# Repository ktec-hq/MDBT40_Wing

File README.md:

# MDBT40 BT4.0 Module Wing
This repo is published under CC-BY-SA 4.0 License

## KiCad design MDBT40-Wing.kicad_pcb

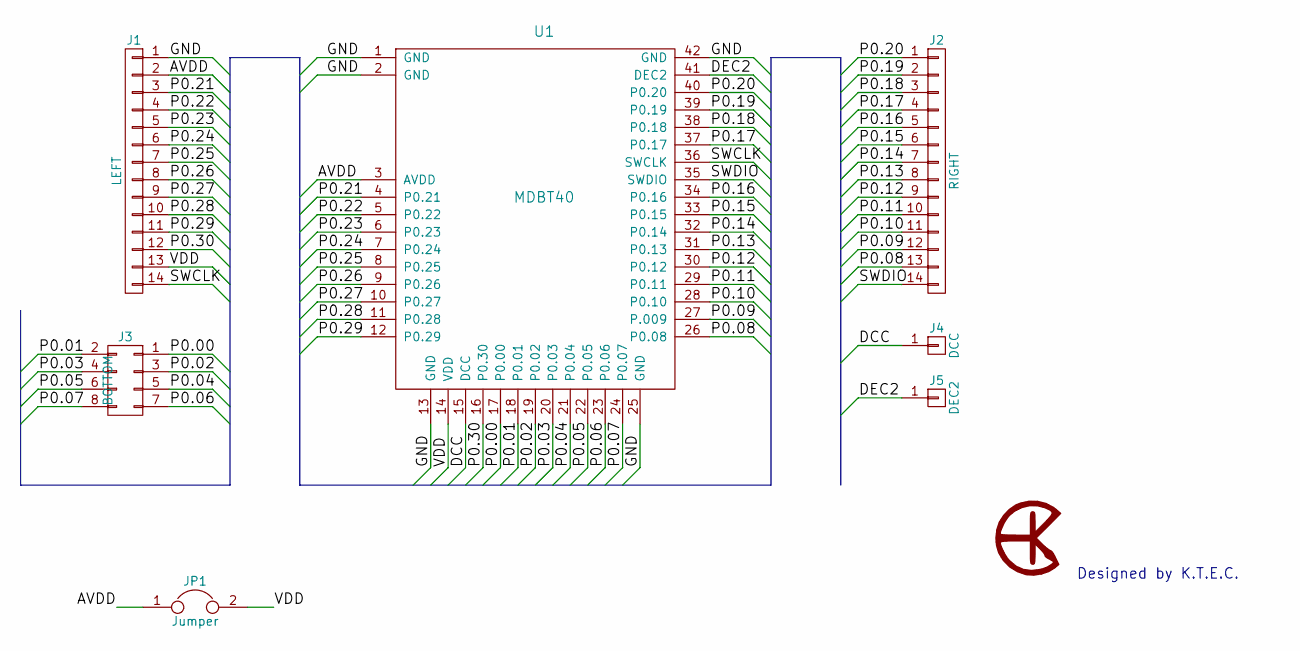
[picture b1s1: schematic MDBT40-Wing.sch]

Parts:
J1: LEFT; Pin_Header_Straight_1x14_Pitch2.54mm
J2: RIGHT; Pin_Header_Straight_1x14_Pitch2.54mm
J3: BOTTOM; Pin_Header_Straight_1x08_Pitch2.54mm
J4: DCC; 1Pin
J5: DEC2; 1Pin
JP1: Jumper; GS2
U1: MDBT40; MDBT40-Carrier

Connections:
/AVDD: J1.2, JP1.1, U1.3 (AVDD)
/DCC: J4.1, U1.15 (DCC)
/DEC2: J5.1, U1.41 (DEC2)
/GND: J1.1, U1.1 (GND), U1.2 (GND), U1.13 (GND), U1.25 (GND), U1.42 (GND)
/P0.00: J3.1, U1.17 (P0.00)
/P0.01: J3.2, U1.18 (P0.01)
/P0.02: J3.3, U1.19 (P0.02)
/P0.03: J3.4, U1.20 (P0.03)
/P0.04: J3.5, U1.21 (P0.04)
/P0.05: J3.6, U1.22 (P0.05)
/P0.06: J3.7, U1.23 (P0.06)
/P0.07: J3.8, U1.24 (P0.07)
/P0.08: J2.13, U1.26 (P0.08)
/P0.09: J2.12, U1.27 (P.009)
/P0.10: J2.11, U1.28 (P0.10)
/P0.11: J2.10, U1.29 (P0.11)
/P0.12: J2.9, U1.30 (P0.12)
/P0.13: J2.8, U1.31 (P0.13)
/P0.14: J2.7, U1.32 (P0.14)
/P0.15: J2.6, U1.33 (P0.15)
/P0.16: J2.5, U1.34 (P0.16)
/P0.17: J2.4, U1.37 (P0.17)
/P0.18: J2.3, U1.38 (P0.18)
/P0.19: J2.2, U1.39 (P0.19)
/P0.20: J2.1, U1.40 (P0.20)
/P0.21: J1.3, U1.4 (P0.21)
/P0.22: J1.4, U1.5 (P0.22)
/P0.23: J1.5, U1.6 (P0.23)
/P0.24: J1.6, U1.7 (P0.24)
/P0.25: J1.7, U1.8 (P0.25)
/P0.26: J1.8, U1.9 (P0.26)
/P0.27: J1.9, U1.10 (P0.27)
/P0.28: J1.10, U1.11 (P0.28)
/P0.29: J1.11, U1.12 (P0.29)
/P0.30: J1.12, U1.16 (P0.30)
/SWCLK: J1.14, U1.36 (SWCLK)
/SWDIO: J2.14, U1.35 (SWDIO)
/VDD: J1.13, JP1.2, U1.14 (VDD)

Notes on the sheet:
Designed by K.T.E.C.

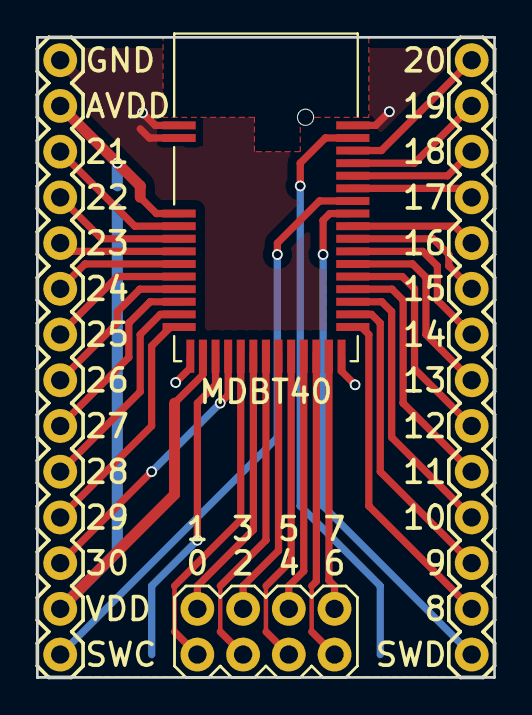
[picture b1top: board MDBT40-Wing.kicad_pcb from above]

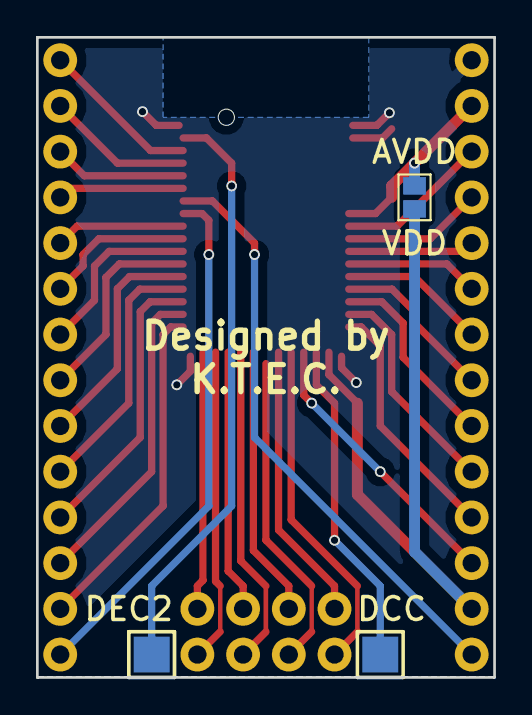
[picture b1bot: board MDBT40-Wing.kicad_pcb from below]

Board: 2 copper layers, 25.4 x 35.6 mm, 7 parts (3 on the bottom side), 38 nets.

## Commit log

2017-03-29 Final touches
2017-03-29 update design
2017-03-31 Design #6
2017-03-31 Optimize edge and route
2017-04-07 Design #7
2017-06-01 Use Adafruit's MDBT40 Mod
2017-06-05 Minor change of trace of GND pins
